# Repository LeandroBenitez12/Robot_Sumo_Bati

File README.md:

# Robot_Sumo_Bati
El robot Sumo "Bati" está diseñado como un proyecto de robótica para poder competir en la LNR.

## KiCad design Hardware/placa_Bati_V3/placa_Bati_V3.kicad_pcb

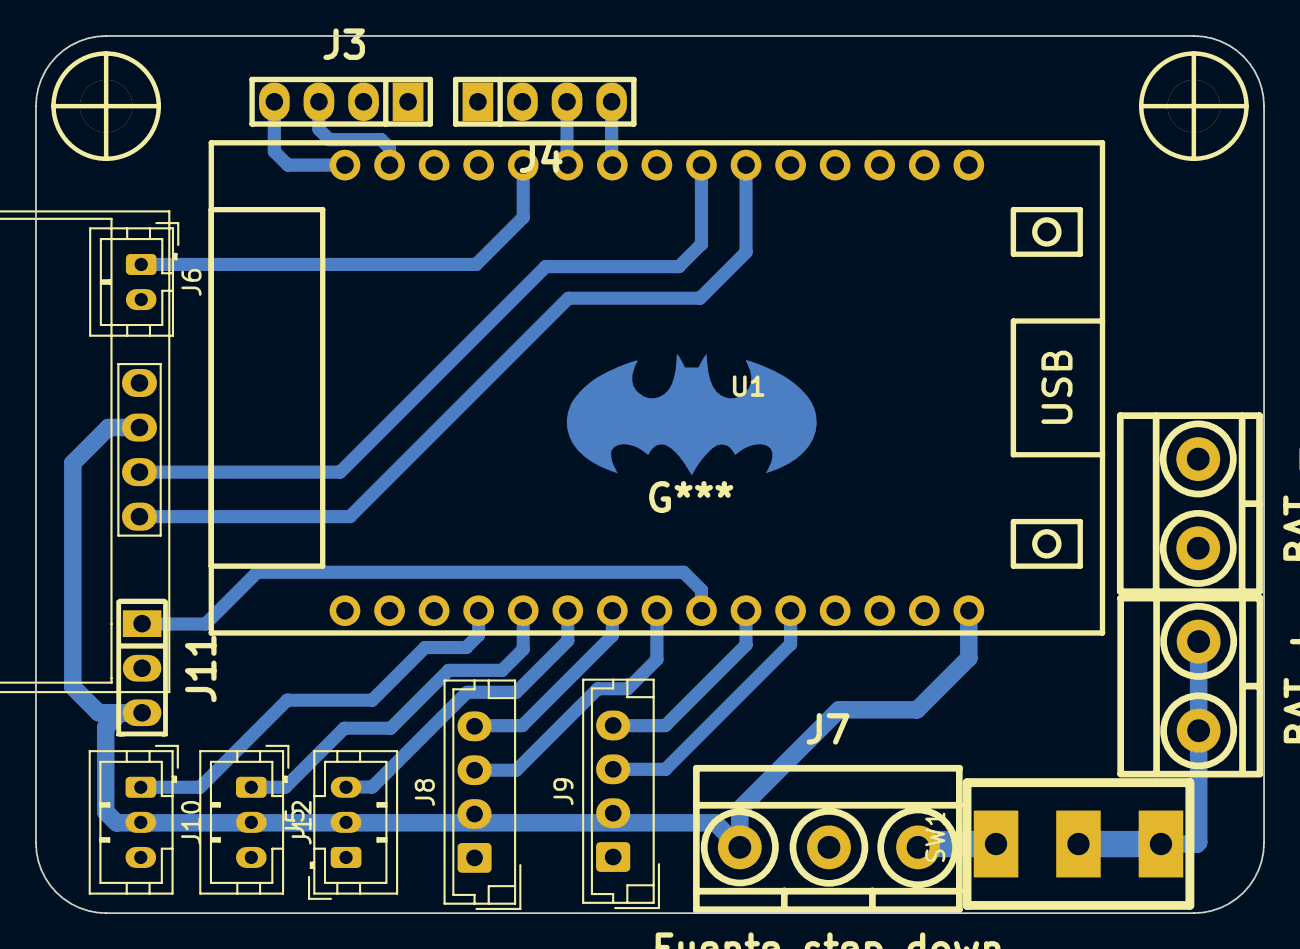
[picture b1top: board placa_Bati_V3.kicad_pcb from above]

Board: 2 copper layers, 70.0 x 50.0 mm, 17 parts (0 on the bottom side), 19 nets.

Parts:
Display1: SSD1306-SSD1306-128x64_OLED; 128x64OLED
H2, H4: Mounting_Hole; Tornillo_M3_8mm
J1: BAT +; BORNERA2_AZUL
J2: BAT -; BORNERA2_AZUL
J3, J4: DRIVER; pin_strip_4
J5: Sharp; JST_PH_B3B-PH-K_1x03_P2.00mm_Vertical
J6: Buzzer; JST_PH_B2B-PH-K_1x02_P2.00mm_Vertical
J7: Fuente step down; BORNERA3_AZUL
J8, J9: Ultrasonido; JST_EH_B4B-EH-A_1x04_P2.50mm_Vertical
J10, J12: CNY70; JST_PH_B3B-PH-K_1x03_P2.00mm_Vertical
J11: Switch est; Pin_Header_3
SW1: SW_SPDT; SW_SPDT_TH_Vertical
U1: ESP32_DevKit_V1_CH9102X

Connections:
+5V: Display1.2 (VCC), J5.2, J7.1, J8.2, J9.2, J10.2, J11.3, J12.2, U1.15 (VIN)
/BUZZER: J6.1, U1.26 (IO21)
/CNY70_FD: J10.1, U1.4 (IO34)
/CNY70_FI: J12.1, U1.5 (IO35)
/ENTER: J11.1, U1.9 (IO26)
/Echo_1: J8.4, U1.7 (IO33)
/Echo_2: J9.4, U1.10 (IO27)
/M1A: J4.4, U1.24 (IO18)
/M1B: J4.3, U1.25 (IO19)
/M2A: J3.4, U1.30 (IO23)
/M2B: J3.3, U1.29 (IO22)
/SCL: Display1.3 (SCL), U1.22 (TX2)
/SDA: Display1.4 (SDA), U1.21 (RX2)
/Trigger_1: J8.3, U1.8 (IO25)
/Trigger_2: J9.3, U1.11 (IO14)
/VBAT: J1.1, J1.2, SW1.2 (B), SW1.3 (C)
/VSTEP: J7.3, SW1.1 (A)
/sharp: J5.3, U1.6 (IO32)
GND: Display1.1 (GND), J2.1, J2.2, J3.1, J4.1, J5.1, J6.2, J7.2, J8.1, J9.1, J10.3, J11.2, J12.3, U1.14 (GND)

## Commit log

2023-08-25 asdasdasd
2023-08-25 principio
2023-09-28 agrego sch BatiXSentdo
2023-10-02 actualizacion del sch de placa sendoXbati
2023-10-26 code main3
2023-10-26 BOTON MOTORES , FALTA SENSORES AGREGAR
